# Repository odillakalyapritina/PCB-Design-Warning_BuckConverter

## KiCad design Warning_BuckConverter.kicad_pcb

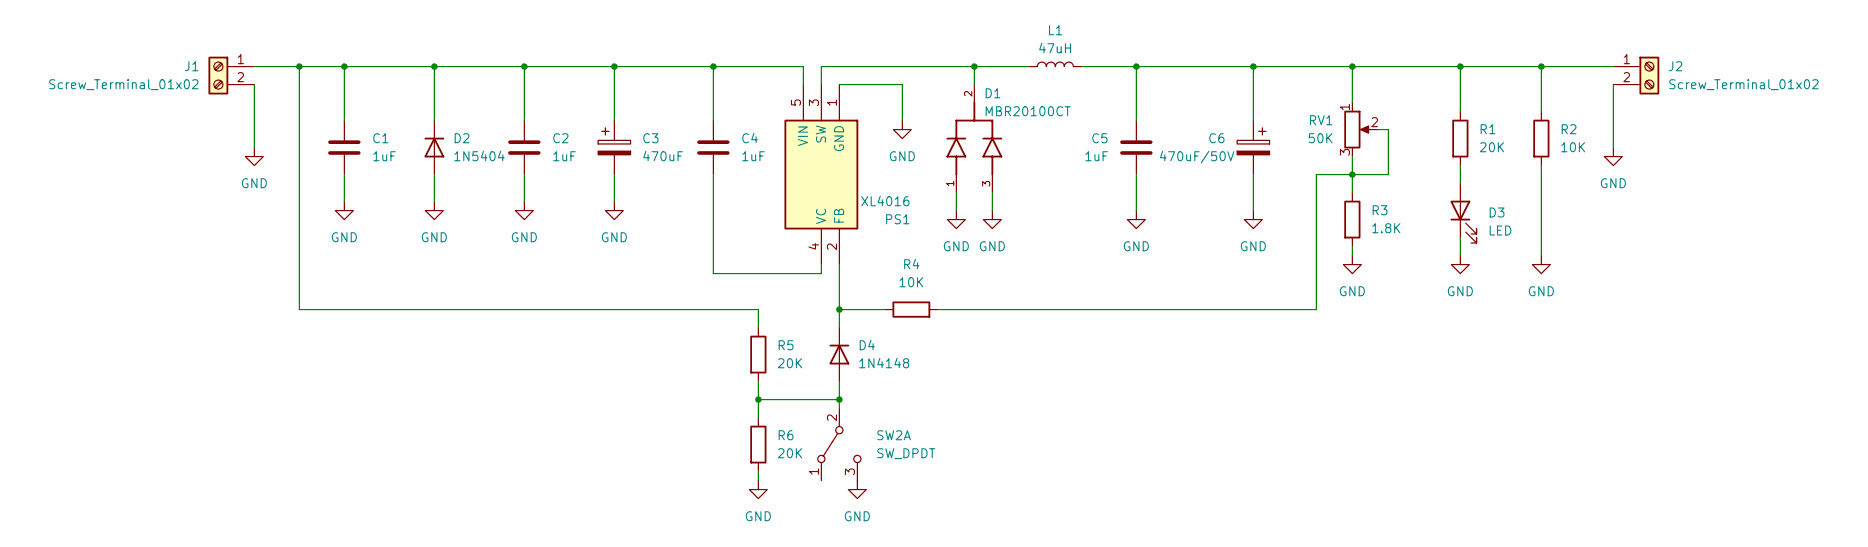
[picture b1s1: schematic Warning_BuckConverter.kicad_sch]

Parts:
C1, C2, C4, C5: 1uF; C_0805_2012Metric
C3: 470uF; CP_Radial_D8.0mm_P3.80mm
C6: 470uF/50V; CP_Radial_D8.0mm_P3.80mm
D1: MBR20100CT; TO-220-3_Vertical; PARTREV 8-2
D2: 1N5404; D_SMA
D3: LED; LED_0805_2012Metric
D4: 1N4148; D_SOD-123
J1, J2: Screw_Terminal_01x02; TerminalBlock_Phoenix_MKDS-1,5-2-5.08_1x02_P5.08mm_Horizont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
L1: 47uH; L_Toroid_Vertical_L16.0mm_W8.0mm_P7.62mm
PS1: XL4016; TO-220-5_Vertical; Manufacturer_Part_Number XL4016
R1, R5, R6: 20K; R_0805_2012Metric
R2, R4: 10K; R_0805_2012Metric
R3: 1.8K; R_0805_2012Metric
RV1: 50K; Potentiometer_Bourns_3296W_Vertical
SW2: SW_DPDT; SW_CuK_JS202011CQN_DPDT_Straight

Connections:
GND: C1.2, C2.2, C3.2, C5.2, C6.2, D1.1, D1.3, D2.2 (A), D3.1 (K), J1.2, J2.2, PS1.1 (GND), R2.2, R3.2, R6.2, SW2.3 (C)
unnamed: C1.1, C2.1, C3.1, C4.1, D2.1 (K), J1.1, PS1.5 (VIN), R5.1
unnamed: D3.2 (A), R1.2
unnamed: D4.2 (A), R5.2, R6.1, SW2.2 (B)
unnamed: D4.1 (K), PS1.2 (FB), R4.1
unnamed: C5.1, C6.1, J2.1, L1.2, R1.1, R2.1, RV1.1
unnamed: D1.2, L1.1, PS1.3 (SW)
unnamed: C4.2, PS1.4 (VC)
unnamed: R3.1, R4.2, RV1.2, RV1.3

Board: 2 copper layers, 22 parts (0 on the bottom side), 9 nets, no tracks yet.

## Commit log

2025-08-28 README.md
